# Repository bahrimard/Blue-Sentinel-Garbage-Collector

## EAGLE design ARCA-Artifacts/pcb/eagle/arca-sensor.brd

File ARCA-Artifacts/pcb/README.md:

# ARCA PCB v1: 1 layer, modular

> **TL;DR:** Ada 2 desain board: **ARCA MAIN v1** (100 × 79 mm, cetak 1 buah) dan **ARCA SENSOR v1** (26 × 23.5 mm, cetak **4 buah**). Board sensor disambung ke board utama pakai kabel 4 pin, jadi posisi tiap HC-SR04 bisa diatur bebas di lambung kapal. Tembaganya cuma di sisi bawah, semua komponen through-hole, dan ada 1 kabel jumper. File Eagle ada di `eagle/`, Gerber siap cetak di `gerber/`, dan PDF 1:1 buat etching sendiri ada di `print/`.
>
> ⚠️ **Firmware untuk PCB pakai pin yang beda dari versi rakit kabel.** Build dengan env **`arca-pcb`** (lihat bagian Firmware).

## Isi folder

| Folder | Isi | Dipakai untuk |
|---|---|---|
| `eagle/` | `arca-main.brd/.sch`, `arca-sensor.brd/.sch`, `arca.lbr` | Dibuka dan diedit di Eagle 9 / Fusion Electronics. Bisa juga di-import ke KiCad |
| `gerber/*-gerber-1layer.zip` | Tembaga bawah, solder mask bawah, silkscreen atas, outline, drill | **Dikirim ke toko cetak PCB 1 layer** |
| `gerber/*-gerber-2layer.zip` | Sama seperti di atas, ditambah tembaga atas | Kalau toko cuma melayani 2 layer. JP1 otomatis jadi jalur tembaga, jadi nggak perlu kabel jumper |
| `print/*ETCHING*.pdf` | Tembaga bawah skala 1:1 (A4) | Etching sendiri pakai metode setrika / toner transfer |
| `print/*PENEMPATAN*.pdf` | Silkscreen dan outline skala 1:1 | Panduan menaruh komponen, sekaligus buat cek ukuran |
| `preview/` | Gambar board | Lihat cepat |
| `kicad/` | Hasil import ke KiCad + laporan DRC | Bukti verifikasi (0 short, 0 jalur putus) |
| `source/` | Skrip generator (`design.py`) | Kalau mau ubah desain, edit di sini lalu generate ulang |

## Cara pesan ke toko cetak

1. Kirim **`arca-main-gerber-1layer.zip`** (1 pcs) dan **`arca-sensor-gerber-1layer.zip`** (4 pcs). Kalau tokonya minta file Eagle, kirim `eagle/arca-main.brd` dan `eagle/arca-sensor.brd`.
2. Spesifikasi: **FR4 1.6 mm, 1 layer (single side), tembaga 1 oz**, lubang tidak perlu plating. Solder mask dan silkscreen opsional.
3. Jalur paling kecil 0.6 mm dan jarak antar-jalur minimal 0.64 mm (board utama) / 0.84 mm (board sensor). Ini aman untuk toko lokal, bahkan untuk etching sendiri.

## Etching sendiri (toner transfer)

1. Print `print/arca-main-ETCHING-tembaga-bawah-1to1.pdf` pakai **printer laser**, skala **100% / Actual size**, jangan "fit to page".
2. **Cek ukuran dulu:** lebar outline harus **100 mm** (board sensor 26 mm). Kalau meleset, perbaiki setting print.
3. Jangan di-mirror. PDF-nya sudah tampak dari atas, dan setelah ditransfer menghadap ke tembaga, hasilnya otomatis benar.
4. Lanjut setrika, etching, lalu bor. Ukuran bor: 0.8 mm (TO-92), 0.9 mm (R/C), 1.0 mm (header), 1.1 mm (L7805), 1.3 mm (terminal), 3.2 mm (lubang baut).

## Sebelum cetak: cek ukuran ESP32

Footprint ESP32 memakai **jarak baris 25.4 mm (1 inch)** untuk DOIT DevKit V1 30 pin. Ada varian DevKit yang jarak barisnya 22.86 mm. Print `print/arca-main-PENEMPATAN-komponen-1to1.pdf`, taruh ESP32 di atas gambar, lalu pastikan dua baris pinnya pas dengan lingkaran pad. Kalau nggak pas, jangan dicetak dulu (desainnya perlu diubah).

## Daftar komponen per board

**ARCA MAIN v1 (1 pcs)**

| Ref | Komponen | Keterangan |
|---|---|---|
| U1 | 2× female header 1×15 (2.54 mm) | Socket ESP32 DevKit V1. Antena ke atas, USB ke bawah |
| U2 | L7805 TO-220 | Berdiri, bagian logam menghadap ke C2 (atas) |
| C1, C2 | Elco / kapasitor 1 µF | Tanda **+** di silkscreen |
| R1 | Resistor 1 kΩ ¼ W | Tidur, pitch 10.16 mm |
| Q1 | BC337 | Sisi datar mengikuti gambar di silkscreen |
| J1 | Terminal screw 3 pin 5.08 | Baterai: **MID** (titik tengah pack), **GND**, **BAT+** |
| J2 | Terminal screw 2 pin 5.08 | Motor conveyor (GND, MID) |
| J3 | Terminal screw 2 pin 5.08 | Power ke L298N (GND, BAT+), pakai kabel tebal |
| J4 | Male header 1×6 | Ke L298N: ENA IN1 IN2 IN3 IN4 ENB (kabel dupont) |
| J5–J8 | Male header 1×4 atau JST-XH 4 pin | Ke 4 board sensor. Urutan pin: **T E G 5V** |
| J9 | Male header 1×2 | Ke buzzer aktif 5 V (+ / −) |
| JP1 | Seutas kabel | Jumper 5V di sisi komponen (lubang "JP1 kabel") |

**ARCA SENSOR v1 (4 pcs)**

| Ref | Komponen | Keterangan |
|---|---|---|
| J2 | Female header 1×4 | Tempat colok HC-SR04 (VCC TRIG ECHO GND) |
| J1 | Male header 1×4 atau JST-XH 4 pin | Kabel ke board utama (**T E G 5V**) |
| R1 | Resistor 470 Ω ¼ W berdiri | Pembagi tegangan ECHO |
| R2 | Resistor 1 kΩ ¼ W berdiri | Pembagi tegangan ECHO |

Kabel sensor: 4 kabel lurus, pin 1 ke pin 1. Kalau pakai JST-XH, pasang konektornya searah di kedua board.

## Kenapa dibagi begini (modular)

- **Board sensor terpisah:** tiap HC-SR04 bisa ditaruh di mana saja (depan-kiri, depan-kanan, bak) cukup dengan kabel. Kalau satu sensor rusak, tinggal ganti board kecilnya.
- **Divider ECHO ada di board sensor:** yang lewat kabel sudah sinyal 3.3 V, jadi aman untuk ESP32 walau kabelnya panjang.
- **Semua koneksi ke luar lewat terminal atau header:** baterai, L298N, conveyor, dan buzzer bisa dicabut-pasang tanpa solder ulang.

## Firmware (pin PCB beda dengan versi kabel)

Supaya PCB 1 layer bisa dirute tanpa jalur silang, pin ESP32-nya diatur ulang:

| Fungsi | Versi kabel (lomba) | **PCB v1** |
|---|---|---|
| ENA / IN1 / IN2 / IN3 / IN4 / ENB | 25 / 13 / 14 / 16 / 17 / 26 | **32 / 33 / 25 / 26 / 27 / 14** |
| Buzzer | 27 | **13** |
| US1 bak-kiri TRIG / ECHO | 4 / 34 | **22 / 23** |
| US2 bak-kanan TRIG / ECHO | 5 / 35 | **19 / 21** |
| US3 depan-kiri TRIG / ECHO | 18 / 32 | **17 / 18** |
| US4 depan-kanan TRIG / ECHO | 19 / 33 | **4 / 16** |

- PlatformIO: pilih env **`arca-pcb`** (menambah flag `-DARCA_PCB_V1`). Env lama `esp32doit-devkit-v1` tetap untuk versi kabel.
- Logika firmware (kendali, failsafe, sensor) sama persis. Test PC `bash test/run_test.sh` menguji kedua varian: **30/30 lulus** untuk masing-masing.

## Verifikasi yang sudah dilakukan

- DRC mandiri (`source/check.py`): semua net tersambung, jarak tembaga antar-net minimal 0.64 mm (main) / 0.84 mm (sensor), dan tidak ada tembaga yang terlalu dekat tepi atau lubang baut.
- File Eagle di-import ke **KiCad 7**, lalu DRC: **0 short, 0 pelanggaran clearance, 0 pad tidak tersambung**. Sisanya cuma peringatan silkscreen yang saling tumpang (kosmetik).
- Netlist skematik = netlist board, dicek otomatis.
- Gerber dan drill dibaca ulang dengan library terpisah (gerbonara): ukuran outline dan jumlah lubang sesuai (main 75 PTH + 4 lubang baut, sensor 12 PTH + 2).
- **Belum:** dibuka langsung di aplikasi Eagle (tidak tersedia di lingkungan Claude), dicetak, atau dirakit.

## Catatan

- Autodesk menghentikan Eagle pada Juni 2026. File `.brd/.sch` ini tetap bisa dibuka di Eagle 9 yang sudah terpasang, di Fusion Electronics, atau di KiCad (File → Import → Eagle).
- Skematik (`.sch`) dibuat otomatis dengan label net (tiap pin diberi label nama net). Rapi secara koneksi, tapi belum digambar ulang dengan tata letak yang cantik.
- GPIO14 (ENB) mengeluarkan sinyal sebentar saat ESP32 boot, sama seperti versi kabel. Nyalakan kapal sambil dipegang.

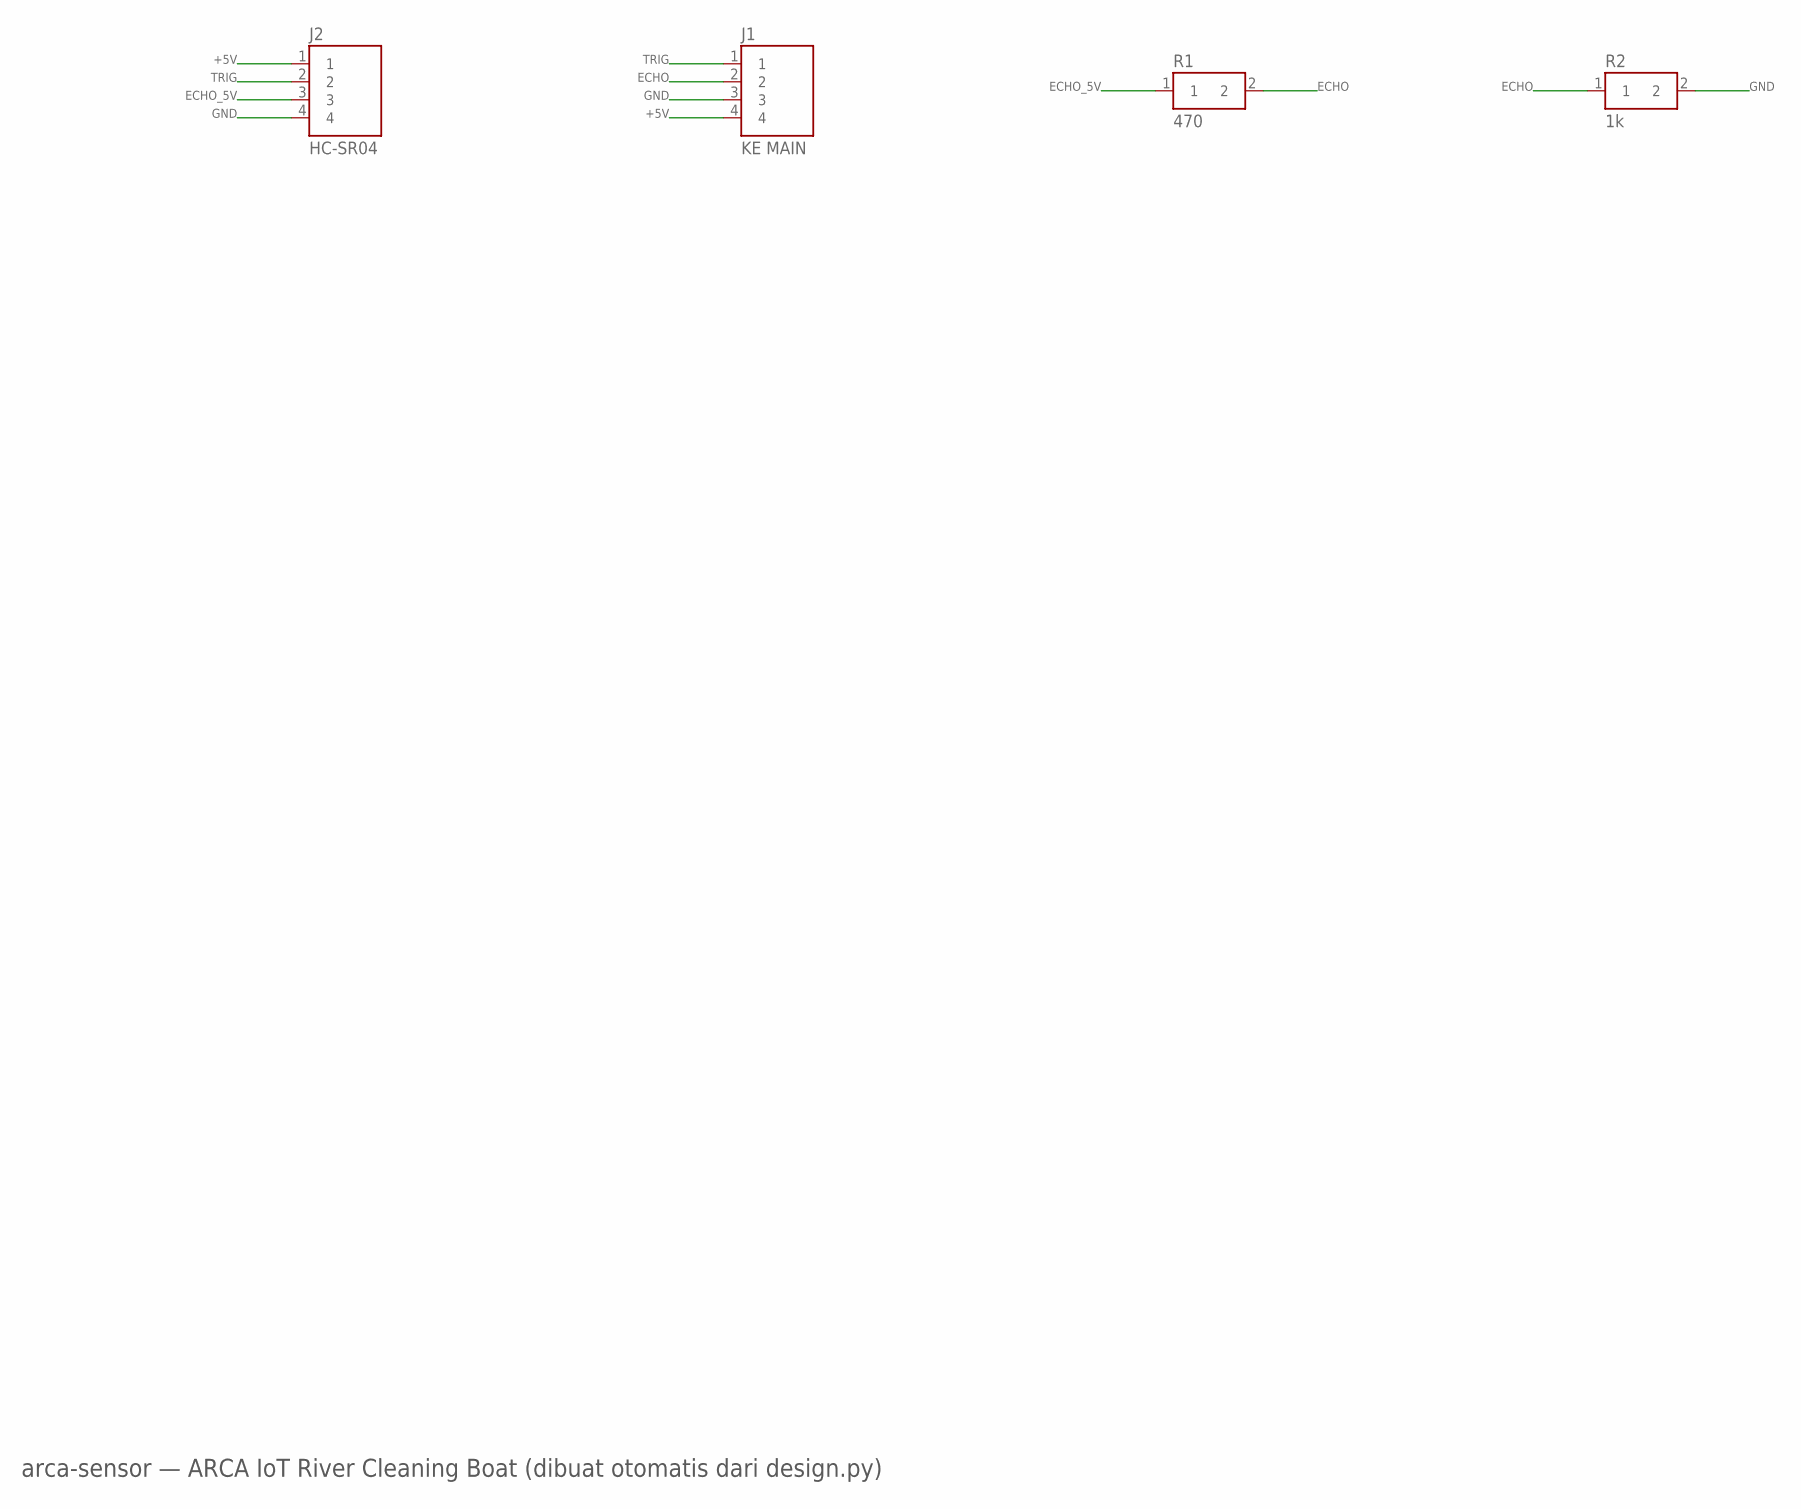
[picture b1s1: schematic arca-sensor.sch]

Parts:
J1: KE MAIN; HDR1X4_H
J2: HC-SR04; HDR1X4_H
R1: 470; RES_V_2.54
R2: 1k; RES_V_2.54

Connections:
+5V: J1.4, J2.1
ECHO: J1.2, R1.2, R2.1
ECHO_5V: J2.3, R1.1
GND: J1.3, J2.4, R2.2
TRIG: J1.1, J2.2

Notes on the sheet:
arca-sensor — ARCA IoT River Cleaning Boat (dibuat otomatis dari design.py)

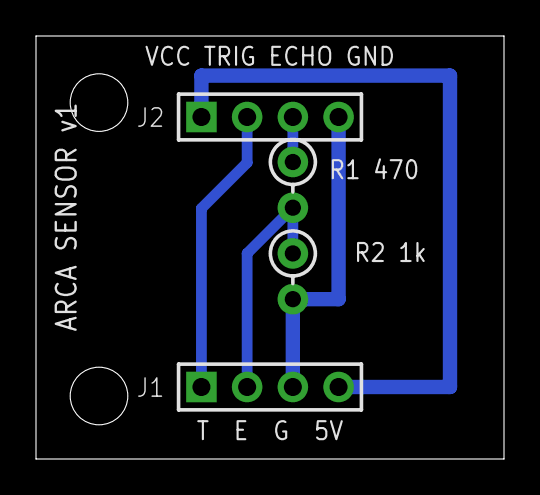
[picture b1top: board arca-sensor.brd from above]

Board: 1 copper layer, 26.0 x 23.5 mm, 4 parts (0 on the bottom side), 5 nets.

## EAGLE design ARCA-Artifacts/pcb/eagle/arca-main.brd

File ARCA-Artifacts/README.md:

# ARCA-Artifacts (Express)

> **TL;DR:** Hasil jadi proyek ARCA. Dokumentasi & alasan ada di `../ARCA-Second-Brain/`.

```
ARCA-Artifacts/
├── web-ui/
│   └── arca-control.html          UI kontrol (= webpage.h). Buka di browser biasa → Mode Simulasi
├── wiring/
│   ├── arca-wiring-diagram.html   diagram sistem + tabel pin-ke-pin + aturan wajib + urutan uji (versi lomba)
│   ├── arca-wiring-diagram.svg    diagram saja (untuk print)
│   ├── arca-wiring-diagram.png    diagram saja (untuk HP)
│   └── arca-wiring-map-per-board.html  detail per-board (21 Sep) — lihat catatan
├── pcb/                           PCB v1 1 layer modular: eagle/, gerber/, print/ (PDF etching 1:1), preview/ — baca pcb/README.md
└── firmware/                      proyek PlatformIO final (env kabel + env arca-pcb)
    ├── platformio.ini
    ├── src/{main.cpp,pins.h,config.h,webpage.h}
    ├── tools/make_webpage_h.py    web-ui/arca-control.html → src/webpage.h
    ├── test/                      uji logika firmware di PC (bash test/run_test.sh) — 30/30 lulus
    └── _arsip-breadboard-test-mode/
```

**Catatan wiring map per‑board (21 Sep):** tabel interkoneksinya masih menyebut kabel “GND ref” tambahan antar board — **abaikan**; aturan terbaru: satu kabel GND per modul langsung ke STAR GND (lihat diagram versi lomba).

**Firmware belum di-compile untuk ESP32** di lingkungan Claude (toolchain tidak tersedia); logikanya sudah diuji di PC (`firmware/test`). Build & upload lewat PlatformIO di laptop; instruksi di `ARCA-Second-Brain/2_Areas/firmware/firmware.md`.

Versi online (private di claude.ai): ARCA Control, ARCA Wiring Review, ARCA Wiring Map — link di README utama vault.

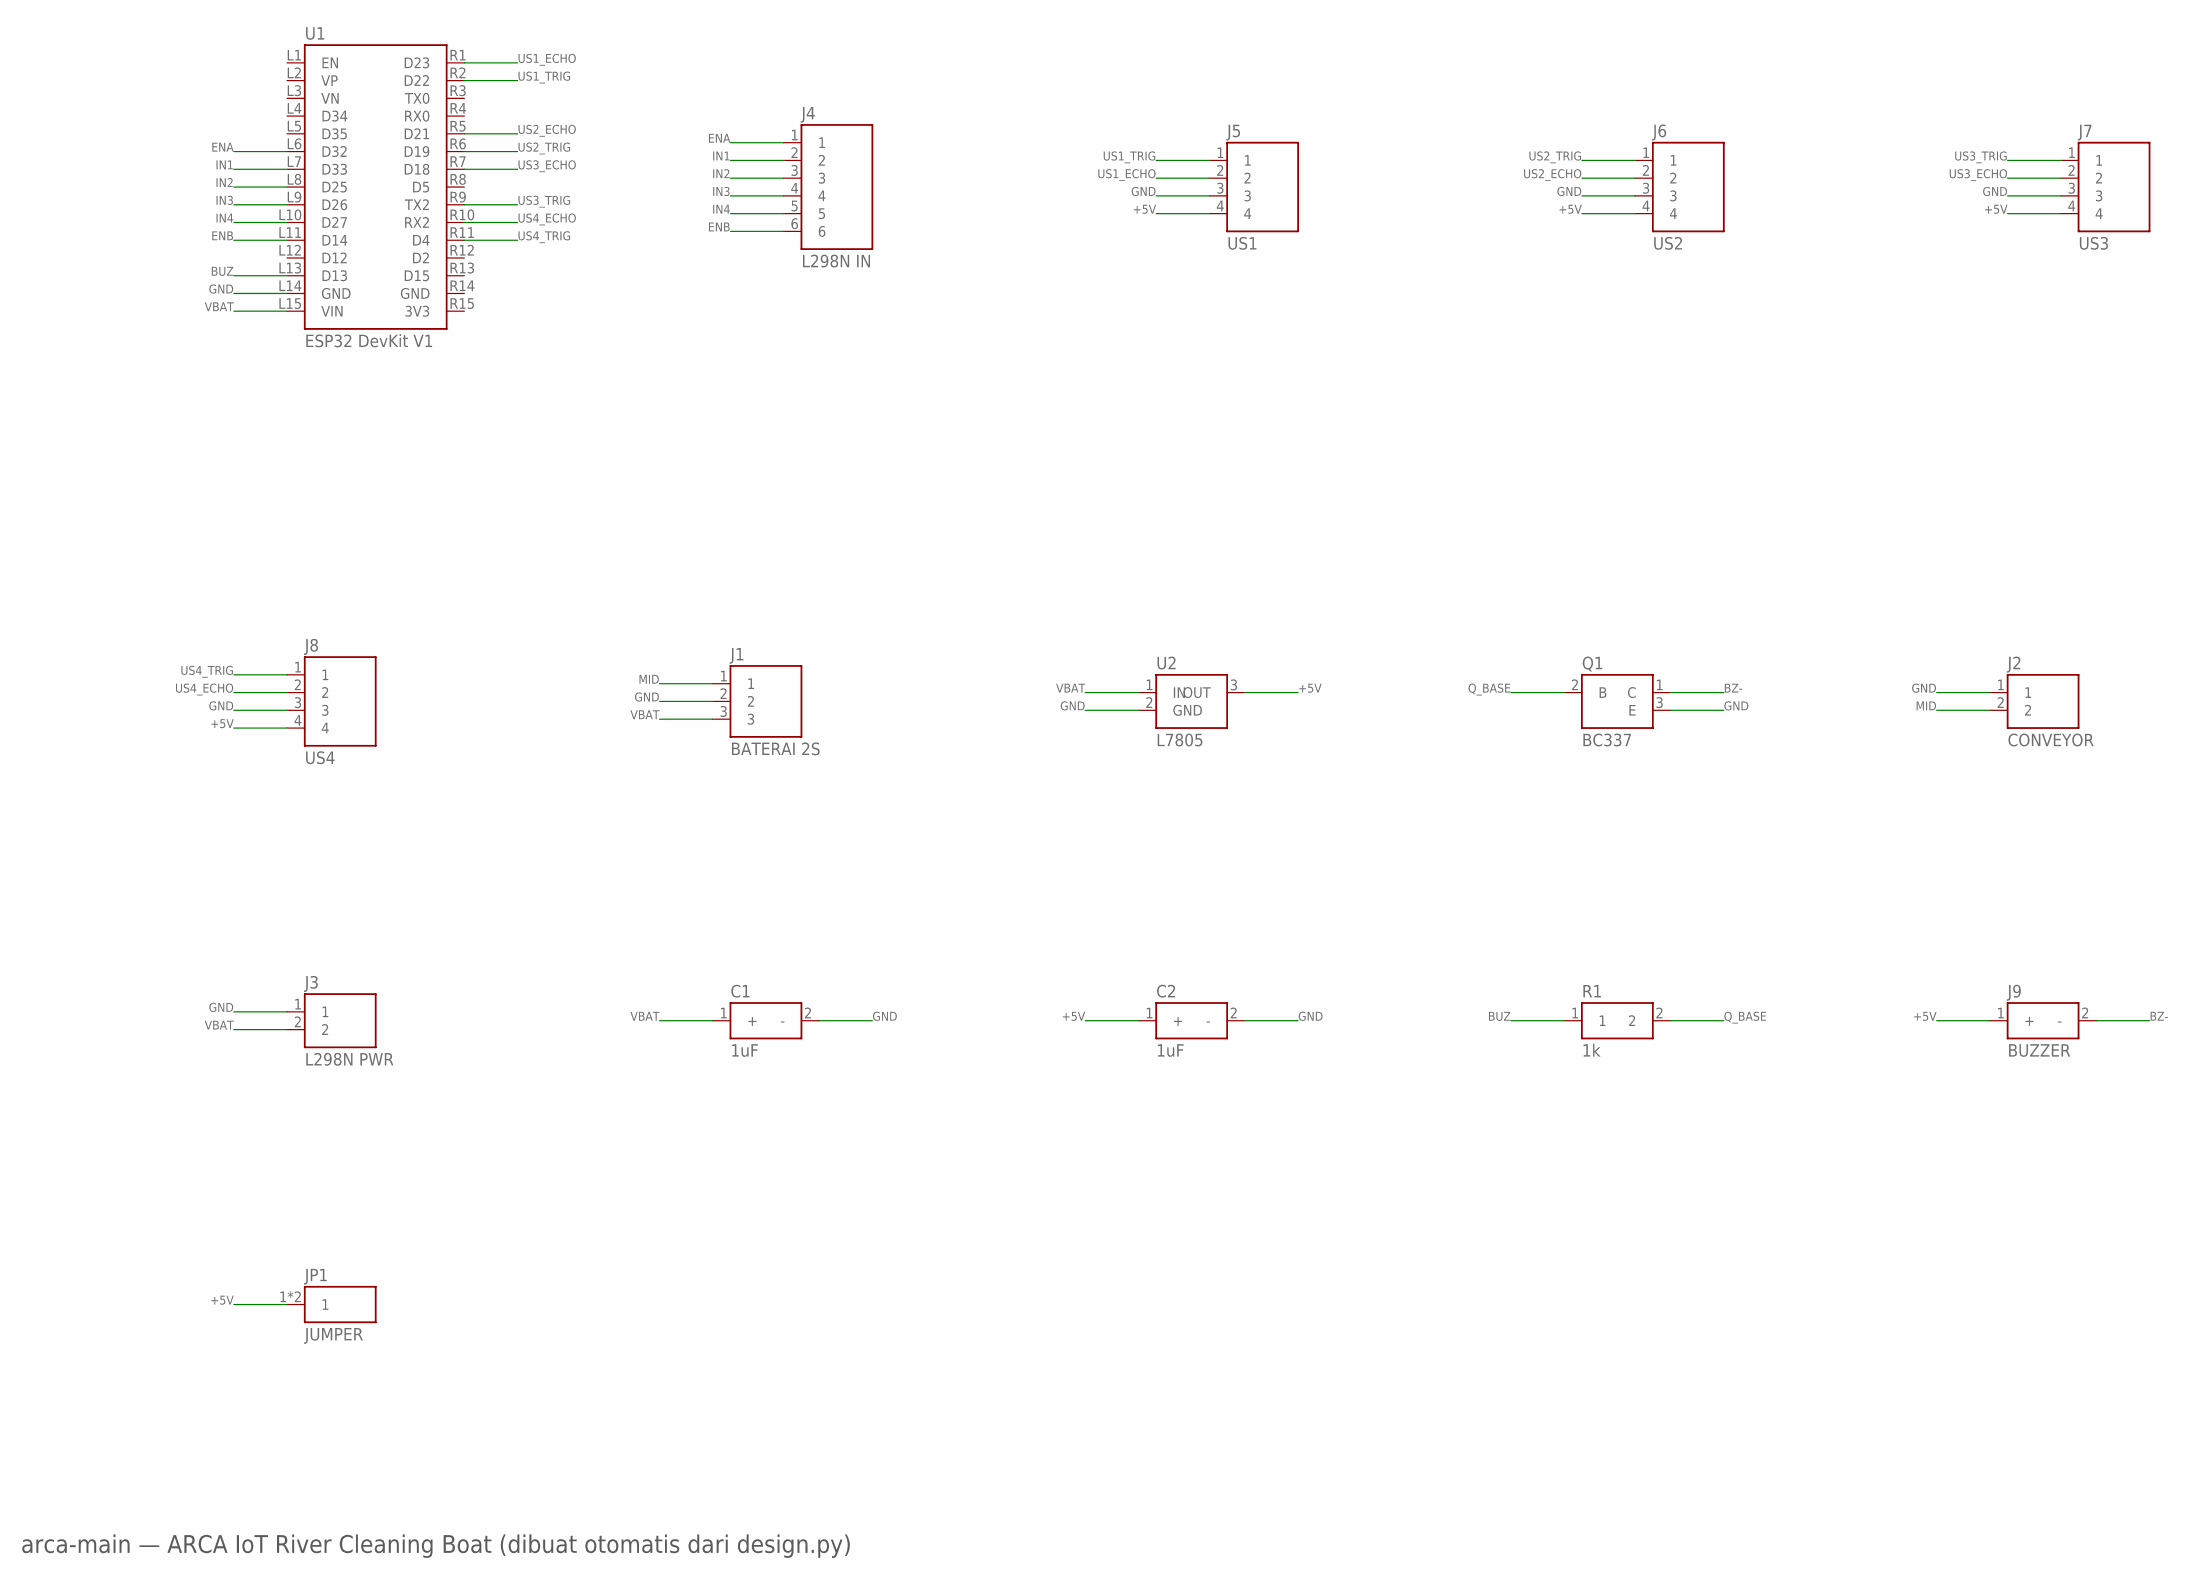
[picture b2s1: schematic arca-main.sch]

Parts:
C1, C2: 1uF; CAP_RAD_2.54
J1: BATERAI 2S; TERM3_508
J2: CONVEYOR; TERM2_508
J3: L298N PWR; TERM2_508
J4: L298N IN; HDR1X6_V
J5: US1; HDR1X4_H
J6: US2; HDR1X4_H
J7: US3; HDR1X4_H
J8: US4; HDR1X4_H
J9: BUZZER; HDR1X2_BZ
JP1: JUMPER; JUMPER_WIRE
Q1: BC337; TO92_INLINE
R1: 1k; RES_AX_10.16
U1: ESP32 DevKit V1; ESP32_DEVKIT_V1_30
U2: L7805; TO220V

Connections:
+5V: C2.1 (+), J5.4, J6.4, J7.4, J8.4, J9.1 (+), JP1.1, JP1.2, U2.3 (OUT)
BUZ: R1.1, U1.L13 (D13)
BZ-: J9.2 (-), Q1.1 (C)
ENA: J4.1, U1.L6 (D32)
ENB: J4.6, U1.L11 (D14)
GND: C1.2 (-), C2.2 (-), J1.2, J2.1, J3.1, J5.3, J6.3, J7.3, J8.3, Q1.3 (E), U1.L14 (GND), U2.2 (GND)
IN1: J4.2, U1.L7 (D33)
IN2: J4.3, U1.L8 (D25)
IN3: J4.4, U1.L9 (D26)
IN4: J4.5, U1.L10 (D27)
MID: J1.1, J2.2
Q_BASE: Q1.2 (B), R1.2
US1_ECHO: J5.2, U1.R1 (D23)
US1_TRIG: J5.1, U1.R2 (D22)
US2_ECHO: J6.2, U1.R5 (D21)
US2_TRIG: J6.1, U1.R6 (D19)
US3_ECHO: J7.2, U1.R7 (D18)
US3_TRIG: J7.1, U1.R9 (TX2)
US4_ECHO: J8.2, U1.R10 (RX2)
US4_TRIG: J8.1, U1.R11 (D4)
VBAT: C1.1 (+), J1.3, J3.2, U1.L15 (VIN), U2.1 (IN)

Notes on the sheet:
arca-main — ARCA IoT River Cleaning Boat (dibuat otomatis dari design.py)

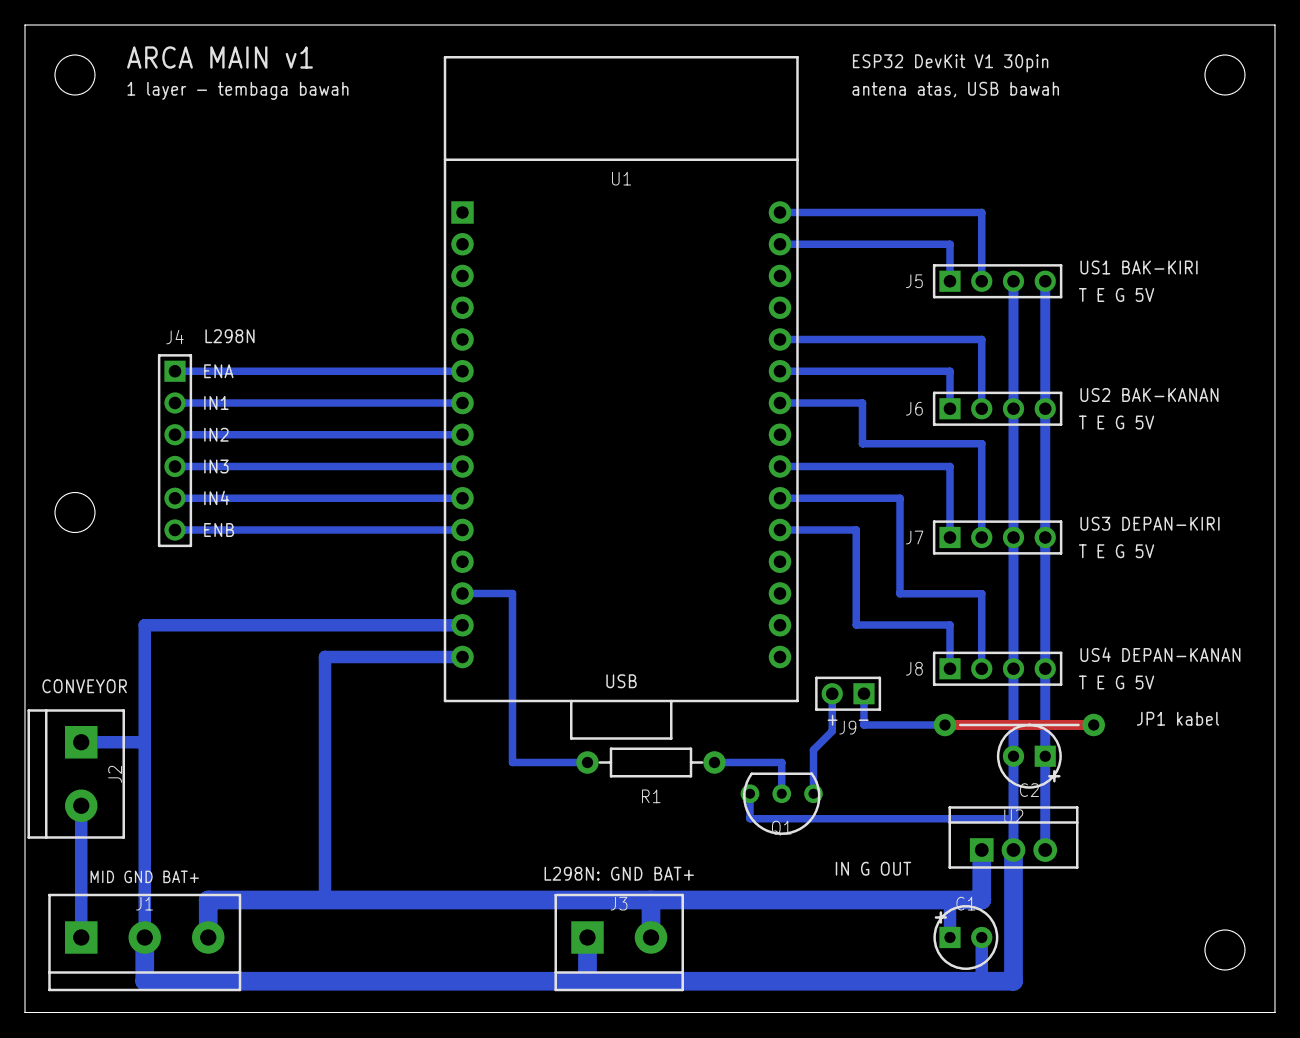
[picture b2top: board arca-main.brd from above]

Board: 1 copper layer, 100.0 x 79.0 mm, 16 parts (0 on the bottom side), 21 nets.

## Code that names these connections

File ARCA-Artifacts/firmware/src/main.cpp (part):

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// ---------- State sensor ----------
// index: 0 = US1 bak-kiri (SAMPAH), 1 = US2 bak-kanan (SAMPAH),
//        2 = US3 depan-kiri (HALANGAN), 3 = US4 depan-kanan (HALANGAN)
const uint8_t TRIG[4] = {PIN_TRIG_BIN_L, PIN_TRIG_BIN_R, PIN_TRIG_FRONT_L, PIN_TRIG_FRONT_R};
const uint8_t ECHO[4] = {PIN_ECHO_BIN_L, PIN_ECHO_BIN_R, PIN_ECHO_FRONT_L, PIN_ECHO_FRONT_R};
float distCm[4] = {NO_ECHO_CM, NO_ECHO_CM, NO_ECHO_CM, NO_ECHO_CM};
float hist[4][3];
uint8_t histIdx[4] = {0, 0, 0, 0};
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  // Kunci motor MATI sebelum apa pun (ENA/ENB mengambang saat boot).
  pinMode(PIN_IN1, OUTPUT); pinMode(PIN_IN2, OUTPUT);
  pinMode(PIN_IN3, OUTPUT); pinMode(PIN_IN4, OUTPUT);
  pinMode(PIN_ENA, OUTPUT); pinMode(PIN_ENB, OUTPUT);
  digitalWrite(PIN_ENA, LOW); digitalWrite(PIN_ENB, LOW);
  ledcSetup(CH_ENA, PWM_FREQ, PWM_RESOLUTION);
  ledcSetup(CH_ENB, PWM_FREQ, PWM_RESOLUTION);
  ledcAttachPin(PIN_ENA, CH_ENA);
  ledcAttachPin(PIN_ENB, CH_ENB);
  stopMotorsNow();
}

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  pinMode(PIN_BUZZER, OUTPUT);
  buzzerWrite(false);
  for (uint8_t i = 0; i < 4; i++) {
    pinMode(TRIG[i], OUTPUT); digitalWrite(TRIG[i], LOW);
    pinMode(ECHO[i], INPUT);
    for (uint8_t k = 0; k < 3; k++) hist[i][k] = NO_ECHO_CM;
  }

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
